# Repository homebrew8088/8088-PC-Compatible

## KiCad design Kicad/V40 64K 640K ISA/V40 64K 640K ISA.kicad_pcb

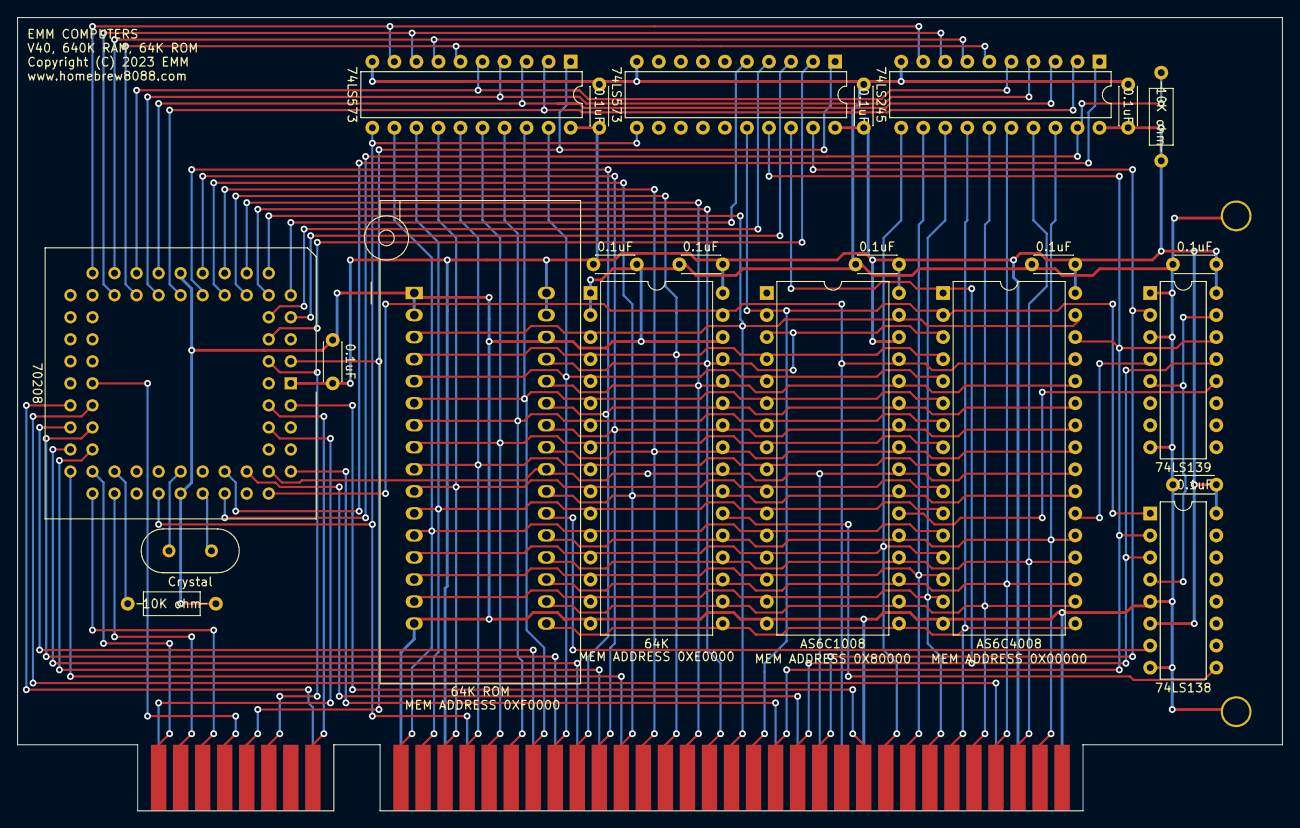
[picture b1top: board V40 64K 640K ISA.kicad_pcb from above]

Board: 2 copper layers, 145.8 x 91.4 mm, 27 parts (0 on the bottom side), 73 nets.

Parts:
C1, C2, C3, C4, C5, C6, C7, C8, C9, C10: 0.1uF; C_Disc_D4.3mm_W1.9mm_P5.00mm
J1: Conn_02x08_Counter_Clockwise; 16_EDGE_CARD_BUS
J9: Bus_ISA_8bit; BUS_8_BIT
R: L; Large_Via
R1, R2: 10K ohm; R_Axial_DIN0207_L6.3mm_D2.5mm_P10.16mm_Horizontal
R#2: L; Large_Via
U1: 64K ROM; DIP_Socket-32_W11.9_W12.7_W15.24_W17.78_W18.5_3M_232-1285-0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
U2: 64K; DIP-32_W15.24mm
U3: AS6C1008; DIP-32_W15.24mm
U4: AS6C4008; DIP-32_W15.24mm
U5: 74LS139; DIP-16_W7.62mm
U6: 74LS138; DIP-16_W7.62mm
U7: 70208; PLCC-68_THT-Socket
U8, U10: 74LS573; DIP-20_W7.62mm
U9: 74LS245; DIP-20_W7.62mm
Y1: Crystal; Crystal_HC18-U_Vertical

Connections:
/64K_ROM_CS: U1.22, U6.7
/128K_CS: U3.22, U5.12
/512K_CS: U4.22, U5.4
/A0: J9.62, U1.12, U2.12, U3.12, U4.12, U10.12
/A1: J9.61, U1.11, U2.11, U3.11, U4.11, U10.13
/A2: J9.60, U1.10, U2.10, U3.10, U4.10, U10.14
/A3: J9.59, U1.9, U2.9, U3.9, U4.9, U10.15
/A4: J9.58, U1.8, U2.8, U3.8, U4.8, U10.16
/A5: J9.57, U1.7, U2.7, U3.7, U4.7, U10.17
/A6: J9.56, U1.6, U2.6, U3.6, U4.6, U10.18
/A7: J9.55, U1.5, U2.5, U3.5, U4.5, U10.19
/A8: J9.54, U1.27, U2.27, U3.27, U4.27, U7.17
/A9: J9.53, U1.26, U2.26, U3.26, U4.26, U7.16
/A10: J9.52, U1.23, U2.23, U3.23, U4.23, U7.15
/A11: J9.51, U1.25, U2.25, U3.25, U4.25, U7.14
/A12: J9.50, U1.4, U2.4, U3.4, U4.4, U7.13
/A13: J9.49, U1.28, U2.28, U3.28, U4.28, U7.12
/A14: J9.48, U1.29, U2.29, U3.3, U4.3, U7.11
/A15: J9.47, U1.3, U2.3, U3.31, U4.31, U7.10
/A16: J9.46, U3.2, U4.2, U6.1, U8.16
/A16_: U7.9, U8.5
/A17: J9.45, U4.30, U5.14, U6.2, U8.17
/A17_: U7.8, U8.4
/A18: J9.44, U4.1, U5.13, U6.3, U8.18
/A18_: U7.7, U8.3
/A19: J9.43, U5.2, U8.19
/A19_: U7.6, U8.2
/AD0: U7.26, U9.9, U10.9
/AD1: U7.25, U9.8, U10.8
/AD2: U7.24, U9.7, U10.7
/AD3: U7.23, U9.6, U10.6
/AD4: U7.22, U9.5, U10.5
/AD5: U7.21, U9.4, U10.4
/AD6: U7.20, U9.3, U10.3
/AD7: U7.19, U9.2, U10.2
/ALE: J9.28, U7.50, U8.11, U10.11
/D0: J9.40, U1.13, U2.13, U3.13, U4.13, U9.11
/D1: J9.39, U1.14, U2.14, U3.14, U4.14, U9.12
/D2: J9.38, U1.15, U2.15, U3.15, U4.15, U9.13
/D3: J9.37, U1.17, U2.17, U3.17, U4.17, U9.14
/D4: J9.36, U1.18, U2.18, U3.18, U4.18, U9.15
/D5: J9.35, U1.19, U2.19, U3.19, U4.19, U9.16
/D6: J9.34, U1.20, U2.20, U3.20, U4.20, U9.17
/D7: J9.33, U1.21, U2.21, U3.21, U4.21, U9.18
/DEN: R2.2, U7.56, U9.19
/DRQ0: J1.12, U7.36
/DTR: U7.57, U9.1
/E0000_CS: U2.22, U6.9
/HF_PCLK: J1.11, U7.44
/HOLD: J1.14, U7.4
/HOLDA: J1.13, U7.3, U8.1, U10.1
/IORD: J9.14, U7.61
/IOWR: J9.13, U7.59
/IRQ1: J1.1, U7.37
/IRQ2: J9.4, U7.38
/IRQ3: J9.25, U7.39
/IRQ4: J9.24, U7.40
/IRQ5: J9.23, U7.41
/IRQ6: J9.22, U7.42
/IRQ7: J9.21, U7.43
/MRD: J9.12, U1.24, U2.24, U3.24, U4.24, U7.62
/MWR: J9.11, U2.31, U3.29, U4.29, U7.60
/NMI: J1.8, U7.66
/POLL: R1.1, U7.47
/RDY1: J9.41, U7.67
/RESET: J1.16, U7.68
/SPK_GO: J1.10, U7.46
/SPK_OUT: J1.9, U7.45
/UPPER_512K: U5.5, U5.15, U6.4
/X1: U7.54, Y1.1
/X2: U7.53, Y1.2
GND: C1.1, C2.1, C3.1, C4.1, C5.1, C6.1, C7.1, C8.1, C9.1, C10.1, J9.1, J9.10, J9.31, R.1, R1.2, R#2.1, U1.1, U1.2, U1.16, U1.30, U2.1, U2.2, U2.16, U2.30, U3.16, U4.16, U5.1, U5.3, U5.8, U6.5, U6.8, U7.18, U7.52, U8.10, U9.10, U10.10
VCC: C1.2, C2.2, C3.2, C4.2, C5.2, C6.2, C7.2, C8.2, C9.2, C10.2, J9.3, J9.29, R2.1, U1.31, U1.32, U2.32, U3.30, U3.32, U4.32, U5.16, U6.6, U6.16, U7.1, U8.20, U9.20, U10.20

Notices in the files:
Kicad/V40 64K 640K ISA/V40 64K 640K ISA.kicad_pcb:
Copyright (C) 2023 EMM
